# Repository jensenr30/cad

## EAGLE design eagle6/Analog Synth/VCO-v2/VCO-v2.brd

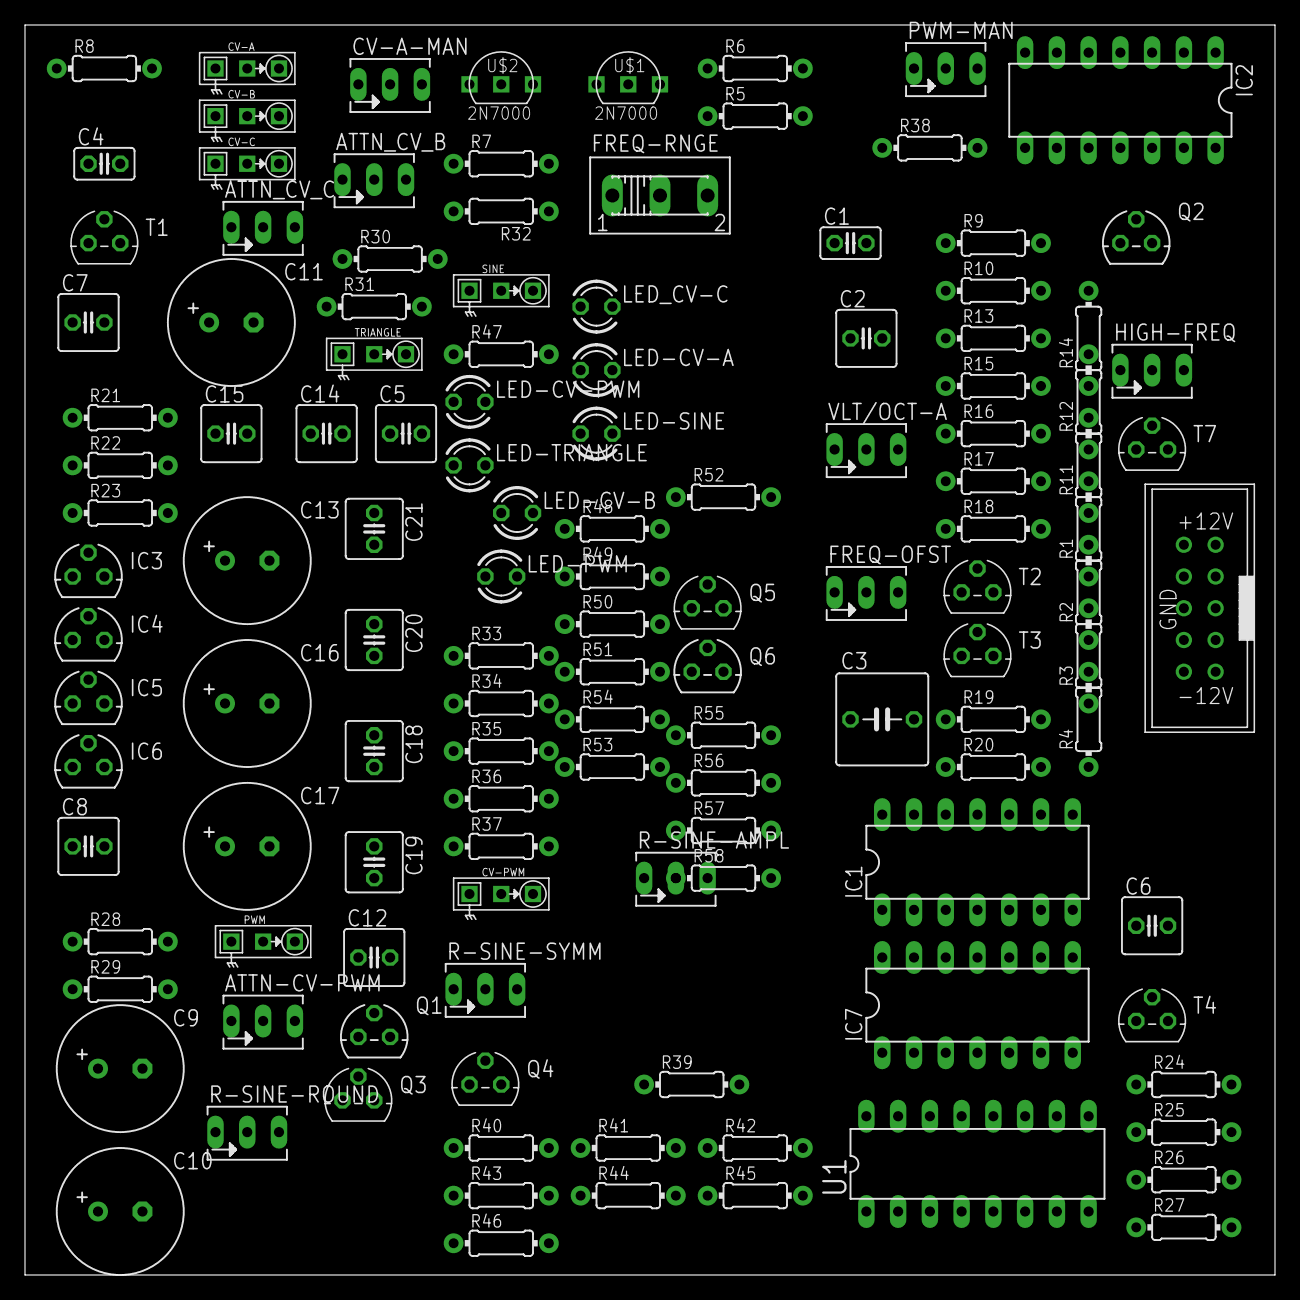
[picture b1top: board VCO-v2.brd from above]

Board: 2 copper layers, 100.0 x 100.0 mm, 127 parts (0 on the bottom side), 79 nets, no tracks yet.

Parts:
ATTN-CV-PWM: 100k log; B64Y
ATTN_CV_B: 100k log; B64Y
ATTN_CV_C: 100k log; B64Y
C1: 10n; C025-025X050
C2: 1u; C025-050X050
C3: 100u; C050-075X075
C4: 100p; C025-025X050
C5: 100p; C025-050X050
C6, C7: 300p; C025-050X050
C8, C12, C14, C15, C18, C19, C20, C21: 0.1u; C025-050X050
C9, C10: 100u; E3,5-10
C11, C13, C16, C17: 10u; E3,5-10
CV-A: I/O; MONO_JACK
CV-A-MAN: 100k lin; B64Y
CV-B: I/O; MONO_JACK
CV-C: I/O; MONO_JACK
CV-PWM: I/O; MONO_JACK
FREQ-OFST: 10k trim; B64Y
FREQ-RNGE: 255SB
HIGH-FREQ: 100k trim; B64Y
IC1, IC2, IC7: TL084P; DIL14
IC3: 78L09; 78LXX
IC4: 78L05; 78LXX
IC5: 79L09\; 79LXX
IC6: 79L05; 79LXX
LED-CV-A: LED3MM
LED-CV-B: LED3MM
LED-CV-PWM: LED3MM
LED-PWM: LED3MM
LED-SINE: LED3MM
LED-TRIANGLE: LED3MM
LED_CV-C: LED3MM
PWM: I/O; MONO_JACK
PWM-MAN: 100k lin; B64Y
Q1, Q2: J310; TO92R
Q3, Q4, Q5: 2N3904; TO92
Q6: 2N3906; TO92
R1, R2, R3, R4, R5, R6, R27, R37, R43, R44, R56, R57: 47k; 0204/7
R7: 150k; 0204/7
R8, R12, R32, R47: 1k; 0204/7
R9, R14, R48, R49, R50, R52, R53, R54: 4.7k; 0204/7
R10, R16, R18, R21, R23, R24, R26, R45, R46: 10k; 0204/7
R11: 22k; 0204/7
R13, R15, R17, R19, R35, R36, R39, R40: 2.2k; 0204/7
R20, R22, R25, R30, R31, R33, R34, R38, R42: 100k; 0204/7
R28, R29: 7.5; 0204/7
R41: 470; 0204/7
R51: 8.2k; 0204/7
R55, R58: 33k; 0204/7
R-SINE-AMPL: 100k trim; B64Y
R-SINE-ROUND: 100k trim; B64Y
R-SINE-SYMM: 10k trim; B64Y
SINE: I/O; MONO_JACK
T1, T2, T3, T4, T7: 2N3904; TO92
TRIANGLE: I/O; MONO_JACK
U1: CA3096; DIL16
U$1, U$2: 2N7000
U$3: EURORACK-POWER
VLT/OCT-A: 10k trim; B64Y

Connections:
+5V: C17.+, C19.1, CV-A-MAN.A, IC4.OUT, PWM-MAN.A, R7.2, U1.10, U1.13
+9V: C11.+, C18.1, IC3.OUT, R16.2, R17.1, R19.2, R43.2, R44.2
+12V: C8.1, C9.+, C14.1, IC1.4, IC2.4, IC3.IN, IC4.IN, Q5.1, R28.2, R58.1
-5V: C1.2, C2.2, C3.2, C16.-, C21.1, CV-A-MAN.E, HIGH-FREQ.E, IC1.12, IC6.OUT, PWM-MAN.E, Q1.S, Q2.S, R22.1, R25.1, T1.3, T2.3, T3.3, U1.5, U1.8
-9V: C13.-, C20.1, IC5.OUT, R9.1, R10.1, R14.1, R42.2
-12V: C10.-, C12.1, C15.1, IC1.11, IC2.11, IC5.IN, IC6.IN, Q6.1, R29.1, R55.2, U1.16
CV-A: IC1.1, IC1.2, LED-CV-A.A, R4.1
CV-B: IC1.6, IC1.7, LED-CV-B.A, R5.1
CV-C: IC1.8, IC1.9, LED_CV-C.A, R6.1
CV-PWM: IC2.13, IC7.1, LED-CV-PWM.K, R38.2
CV_SUM_POINT: FREQ-OFST.A, IC1.13, R5.2, R6.2, R11.1, R12.1, R27.2, VLT/OCT-A.E, VLT/OCT-A.S
GND: ATTN-CV-PWM.A, ATTN_CV_B.A, ATTN_CV_C.A, C8.2, C9.-, C10.+, C11.-, C12.2, C13.+, C14.2, C15.2, C16.+, C17.-, C18.2, C19.2, C20.2, C21.2, CV-A.P$1, CV-B.P$1, CV-B.P$3, CV-C.P$1, CV-C.P$3, CV-PWM.P$1, CV-PWM.P$3, IC2.3, IC3.GND, IC4.GND, IC5.GND, IC6.GND, IC7.3, IC7.12, PWM.P$1, R21.2, R24.2, R30.1, R36.1, R39.2, R40.2, R45.1, R56.1, R57.2, SINE.P$1, T4.1, T4.3, T7.1, T7.3, TRIANGLE.P$1, U$3.P$3, U$3.P$4, U$3.P$5, U$3.P$6, U$3.P$7, U$3.P$8
unnamed: CV-A.P$3, CV-A-MAN.S
unnamed: CV-A.P$2, R1.1
unnamed: IC1.3, IC1.5, IC1.10, R1.2, R2.2, R3.2
unnamed: ATTN_CV_C.S, R3.1
unnamed: Q6.2, R55.1, R56.2
unnamed: ATTN_CV_B.S, R2.1
unnamed: LED-CV-PWM.A, R53.1
unnamed: ATTN_CV_B.E, CV-B.P$2
unnamed: ATTN_CV_C.E, CV-C.P$2
unnamed: Q5.3, R53.2
unnamed: U1.6, U1.11, U1.12, U1.14
unnamed: R4.2, VLT/OCT-A.A
unnamed: C4.2, IC2.1, R8.1
unnamed: R8.2, U1.2, U1.4, U1.7
unnamed: R16.1, T1.1, T2.2
unnamed: FREQ-OFST.E, R14.2
unnamed: C2.1, FREQ-RNGE.3
unnamed: U1.9, U$1.S
unnamed: U1.15, U$2.D
unnamed: C4.1, IC2.2, R7.1, U1.3
unnamed: C3.1, FREQ-RNGE.1
unnamed: R9.2, R10.2, R13.1, R18.1, T1.2
unnamed: R13.2, R15.1
unnamed: Q1.D, R21.1, R23.1
unnamed: C7.2, Q1.G, R22.2, T7.2
unnamed: IC2.9, R30.2, R31.2
unnamed: R32.1, TRIANGLE.P$2
unnamed: Q2.D, R24.1, R26.1
unnamed: C5.2, R20.1, T3.2
unnamed: C6.2, Q2.G, R25.2, T4.2
unnamed: HIGH-FREQ.A, R23.2, R26.2
unnamed: HIGH-FREQ.S, R27.1
unnamed: R28.1, U$3.P$1, U$3.P$2
unnamed: R29.2, U$3.P$9, U$3.P$10
unnamed: Q6.3, R48.2, R49.2, R50.2, R51.2, R52.2, R54.2
unnamed: Q3.2, R39.1, R-SINE-ROUND.E
unnamed: PWM.P$2, R35.2, R36.2
unnamed: IC7.5, R37.2
unnamed: ATTN-CV-PWM.E, IC7.6, IC7.7
unnamed: CV-PWM.P$2, R37.1
unnamed: ATTN-CV-PWM.S, R34.1
unnamed: IC7.2, R33.2, R34.2, R38.1
unnamed: Q5.2, R57.1, R58.2
unnamed: PWM-MAN.S, R33.1
unnamed: Q4.2, R40.1
unnamed: Q3.3, R41.1, R-SINE-SYMM.A
unnamed: Q4.3, R41.2, R-SINE-SYMM.E
unnamed: R42.1, R-SINE-SYMM.S
unnamed: IC7.9, Q3.1, R43.1, R46.1
unnamed: IC7.8, R46.2, R-SINE-AMPL.A
unnamed: IC7.10, Q4.1, R44.1, R45.2
unnamed: LED-CV-A.K, R52.1
unnamed: IC7.13, R-SINE-AMPL.S
unnamed: R47.2, SINE.P$2
unnamed: LED-CV-B.K, R48.1
unnamed: LED_CV-C.K, R49.1
unnamed: LED-TRIANGLE.K, R50.1
unnamed: LED-PWM.K, R51.1
unnamed: LED-SINE.K, R54.1
NPN_CV: IC1.14, R11.2, R12.2, U1.1
PWM: IC2.14, LED-PWM.A, R35.1
RAMP_DOWN: C5.1, C6.1, R17.2, R18.2, R20.2, T2.1, U$1.G
RAMP_UP: C7.1, R19.1, T3.1, U$2.G
SINE: IC7.14, LED-SINE.A, R47.1, R-SINE-AMPL.E
TRIANGLE: IC2.8, IC2.12, LED-TRIANGLE.A, R31.1, R32.2, R-SINE-ROUND.A, R-SINE-ROUND.S
TRIANGLE-RAW: C1.1, FREQ-RNGE.2, IC2.5, U$1.D, U$2.S
V-CAP-BUFF: IC2.6, IC2.7, IC2.10, R15.2

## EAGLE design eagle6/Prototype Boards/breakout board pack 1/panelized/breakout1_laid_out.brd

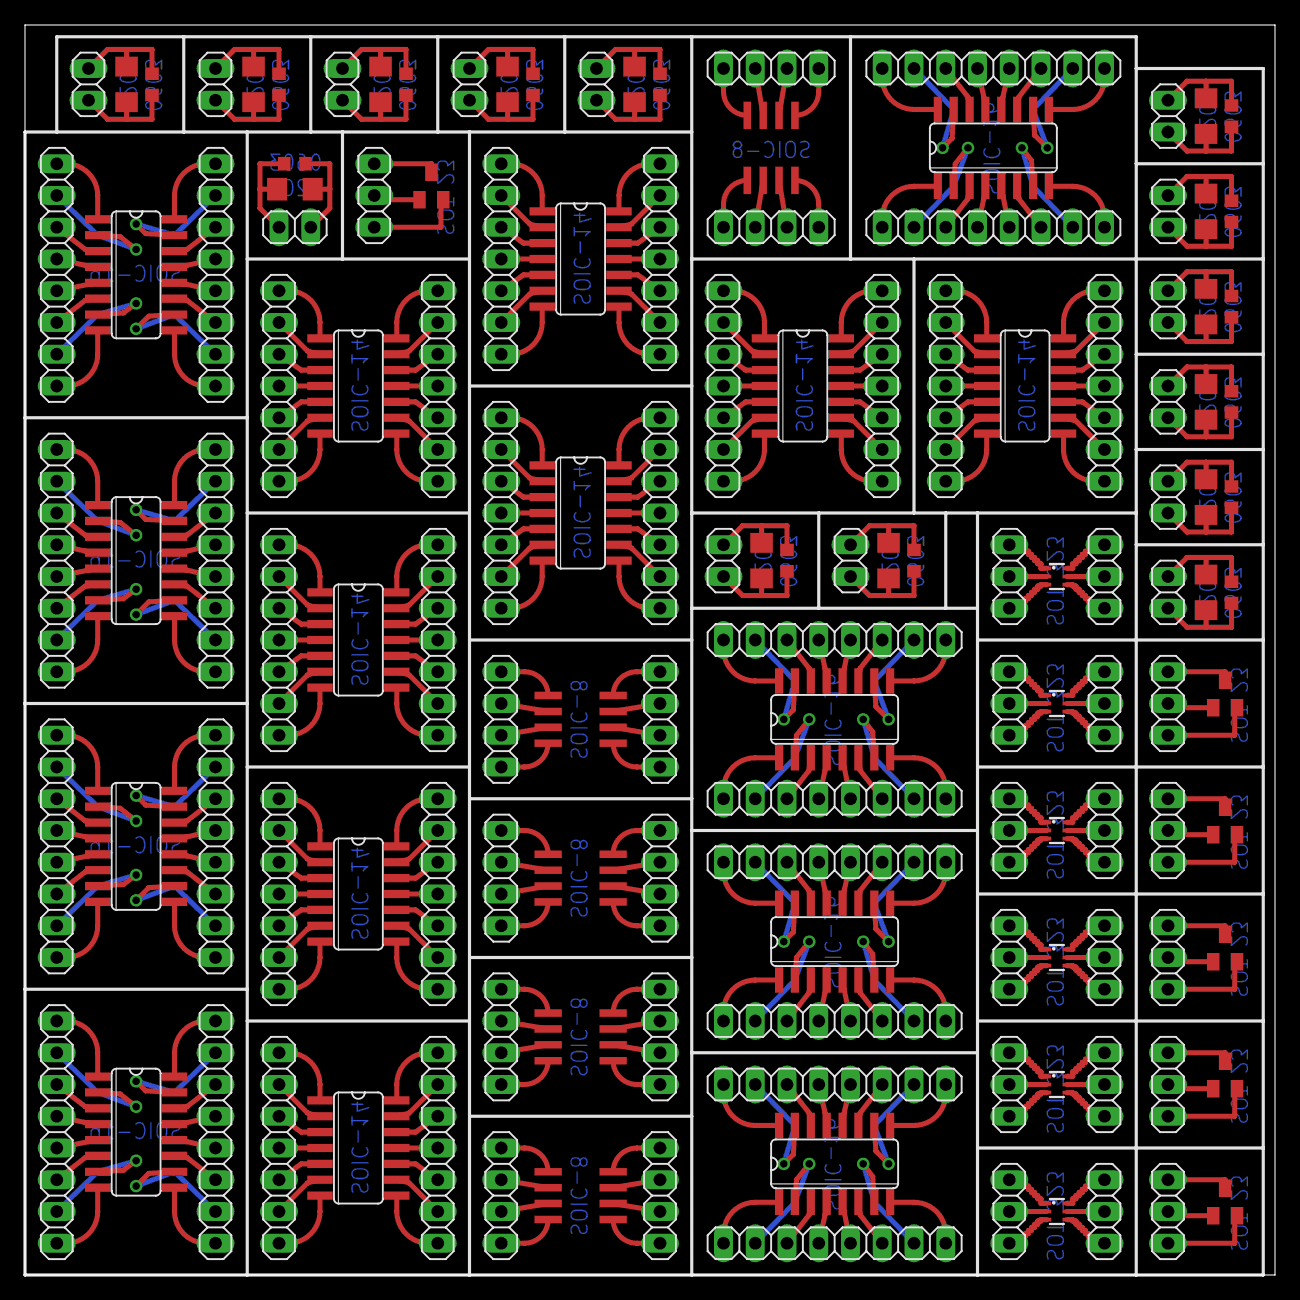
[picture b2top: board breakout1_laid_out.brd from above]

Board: 2 copper layers, 100.0 x 100.0 mm, 135 parts (0 on the bottom side), 362 nets.

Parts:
IC1, IC4, IC5, IC13, IC21, IC22, IC23, IC26: 74LS151D; SO16
IC3, IC10, IC17, IC18, IC27: NE555D; SO08
IC7, IC8, IC14, IC15, IC16, IC19, IC24, IC25: 74LS03D; SO14
JP1, JP2, JP31, JP32, JP49, JP50, JP51, JP52, JP53, JP66, JP67, JP68, JP69, JP70, JP71, JP72, JP73, JP91: 1X03
JP5, JP6, JP11, JP12, JP13, JP14, JP41, JP42, JP74, JP75, JP76, JP77, JP78, JP79, JP86, JP87: 1X08
JP9, JP10, JP35, JP36, JP57, JP58, JP59, JP60, JP88, JP89: 1X04
JP17, JP18, JP19, JP20, JP43, JP44, JP45, JP46, JP47, JP48, JP61, JP62, JP82, JP83, JP84, JP85: 1X07
JP23, JP24, JP25, JP54, JP55, JP56, JP63, JP65, JP80, JP81, JP92, JP93, JP94, JP95: 1X02
Q5, Q6, Q7, Q8, Q9, Q10: BCX70SMD; SOT23
R1, R5, R7, R9, R11, R13, R15, R17, R19, R21, R23, R25, R27, R29: R0603
R3, R6, R8, R10, R12, R14, R16, R18, R20, R22, R24, R26, R28, R30: R1206
U$1, U$3, U$5, U$6, U$7, U$8: DMMT3904W; SOT363

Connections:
unnamed: JP1.3, U$1.1
unnamed: JP1.2, U$1.2
unnamed: JP1.1, U$1.3
unnamed: JP2.1, U$1.4
unnamed: JP2.2, U$1.5
unnamed: JP2.3, U$1.6
unnamed: IC4.1, JP12.1
unnamed: IC1.1, JP6.1
unnamed: IC1.2, JP6.2
unnamed: IC1.3, JP6.3
unnamed: IC1.4, JP6.4
unnamed: IC1.7, JP6.7
unnamed: IC1.5, JP6.5
unnamed: IC1.6, JP6.6
unnamed: IC1.8, JP6.8
unnamed: IC1.9, JP5.1
unnamed: IC1.10, JP5.2
unnamed: IC1.11, JP5.3
unnamed: IC1.12, JP5.4
unnamed: IC1.13, JP5.5
unnamed: IC1.14, JP5.6
unnamed: IC1.15, JP5.7
unnamed: IC1.16, JP5.8
unnamed: IC3.1, JP9.1
unnamed: IC3.2, JP9.2
unnamed: IC3.4, JP9.4
unnamed: IC3.3, JP9.3
unnamed: IC3.5, JP10.1
unnamed: IC3.6, JP10.2
unnamed: IC3.7, JP10.3
unnamed: IC3.8, JP10.4
unnamed: IC4.2, JP12.2
unnamed: IC4.3, JP12.3
unnamed: IC4.4, JP12.4
unnamed: IC4.7, JP12.7
unnamed: IC4.5, JP12.5
unnamed: IC4.6, JP12.6
unnamed: IC4.8, JP12.8
unnamed: IC4.9, JP11.1
unnamed: IC4.10, JP11.2
unnamed: IC4.11, JP11.3
unnamed: IC4.12, JP11.4
unnamed: IC4.13, JP11.5
unnamed: IC4.14, JP11.6
unnamed: IC4.16, JP11.8
unnamed: IC4.15, JP11.7
unnamed: IC5.1, JP14.1
unnamed: IC5.2, JP14.2
unnamed: IC5.3, JP14.3
unnamed: IC5.4, JP14.4
unnamed: IC5.7, JP14.7
unnamed: IC5.5, JP14.5
unnamed: IC5.6, JP14.6
unnamed: IC5.8, JP14.8
unnamed: IC5.9, JP13.1
unnamed: IC5.10, JP13.2
unnamed: IC5.11, JP13.3
unnamed: IC5.12, JP13.4
unnamed: IC5.13, JP13.5
unnamed: IC5.14, JP13.6
unnamed: IC5.16, JP13.8
unnamed: IC5.15, JP13.7
unnamed: IC7.1, JP17.1
unnamed: IC7.2, JP17.2
unnamed: IC7.4, JP17.4
unnamed: IC7.5, JP17.5
unnamed: IC7.6, JP17.6
unnamed: IC7.3, JP17.3
unnamed: IC7.8, JP18.1
unnamed: IC7.9, JP18.2
unnamed: IC7.10, JP18.3
unnamed: IC7.11, JP18.4
unnamed: IC7.12, JP18.5
unnamed: IC7.13, JP18.6
unnamed: IC7.14, JP18.7
unnamed: IC7.7, JP17.7
unnamed: IC8.1, JP19.1
unnamed: IC8.2, JP19.2
unnamed: IC8.4, JP19.4
unnamed: IC8.5, JP19.5
unnamed: IC8.6, JP19.6
unnamed: IC8.3, JP19.3
unnamed: IC8.8, JP20.1
unnamed: IC8.9, JP20.2
unnamed: IC8.10, JP20.3
unnamed: IC8.11, JP20.4
unnamed: IC8.12, JP20.5
unnamed: IC8.13, JP20.6
unnamed: IC8.14, JP20.7
unnamed: IC8.7, JP19.7
unnamed: JP23.1, R1.2, R3.2
unnamed: JP23.2, R1.1, R3.1
unnamed: JP24.1, R5.2, R6.2
unnamed: JP24.2, R5.1, R6.1
unnamed: JP25.1, R7.2, R8.2
unnamed: JP25.2, R7.1, R8.1
unnamed: JP31.1, U$3.3
unnamed: JP31.2, U$3.2
unnamed: JP31.3, U$3.1
unnamed: JP32.1, U$3.4
unnamed: JP32.2, U$3.5
unnamed: JP32.3, U$3.6
unnamed: IC10.1, JP35.1
unnamed: IC10.2, JP35.2
unnamed: IC10.4, JP35.4
unnamed: IC10.3, JP35.3
unnamed: IC10.5, JP36.1
unnamed: IC10.6, JP36.2
unnamed: IC10.7, JP36.3
unnamed: IC10.8, JP36.4
unnamed: IC13.1, JP42.1
unnamed: IC13.2, JP42.2
unnamed: IC13.3, JP42.3
unnamed: IC13.4, JP42.4
unnamed: IC13.7, JP42.7
unnamed: IC13.5, JP42.5
unnamed: IC13.6, JP42.6
unnamed: IC13.8, JP42.8
unnamed: IC13.9, JP41.1
unnamed: IC13.10, JP41.2
unnamed: IC13.11, JP41.3
unnamed: IC13.12, JP41.4
unnamed: IC13.13, JP41.5
unnamed: IC13.14, JP41.6
unnamed: IC13.16, JP41.8
unnamed: IC13.15, JP41.7
unnamed: IC14.1, JP43.1
unnamed: IC14.2, JP43.2
unnamed: IC14.4, JP43.4
unnamed: IC14.5, JP43.5
unnamed: IC14.6, JP43.6
unnamed: IC14.3, JP43.3
unnamed: IC14.8, JP44.1
unnamed: IC14.9, JP44.2
unnamed: IC14.10, JP44.3
unnamed: IC14.11, JP44.4
unnamed: IC14.12, JP44.5
unnamed: IC14.13, JP44.6
unnamed: IC14.14, JP44.7
unnamed: IC14.7, JP43.7
unnamed: IC15.1, JP45.1
unnamed: IC15.2, JP45.2
unnamed: IC15.4, JP45.4
unnamed: IC15.5, JP45.5
unnamed: IC15.6, JP45.6
unnamed: IC15.3, JP45.3
unnamed: IC15.8, JP46.1
unnamed: IC15.9, JP46.2
unnamed: IC15.10, JP46.3
unnamed: IC15.11, JP46.4
unnamed: IC15.12, JP46.5
unnamed: IC15.13, JP46.6
unnamed: IC15.14, JP46.7
unnamed: IC15.7, JP45.7
unnamed: IC16.1, JP47.1
unnamed: IC16.2, JP47.2
unnamed: IC16.4, JP47.4
unnamed: IC16.5, JP47.5
unnamed: IC16.6, JP47.6
unnamed: IC16.3, JP47.3
unnamed: IC16.8, JP48.1
unnamed: IC16.9, JP48.2
unnamed: JP49.2, Q5.1
unnamed: JP49.3, Q5.2
unnamed: JP49.1, Q5.3
unnamed: JP50.2, Q6.1
unnamed: JP50.3, Q6.2
unnamed: JP50.1, Q6.3
unnamed: JP51.2, Q7.1
unnamed: JP51.3, Q7.2
unnamed: JP51.1, Q7.3
unnamed: JP52.2, Q8.1
unnamed: JP52.3, Q8.2
unnamed: JP52.1, Q8.3
unnamed: JP53.2, Q9.1
unnamed: JP53.3, Q9.2
unnamed: JP53.1, Q9.3
unnamed: JP54.1, R13.2, R14.2
unnamed: JP54.2, R13.1, R14.1
unnamed: JP65.1, R15.2, R16.2
unnamed: JP55.1, R9.2, R10.2
unnamed: JP55.2, R9.1, R10.1
unnamed: JP56.1, R11.2, R12.2
unnamed: JP56.2, R11.1, R12.1
unnamed: JP65.2, R15.1, R16.1
unnamed: JP66.1, U$5.3
unnamed: IC17.1, JP57.1
unnamed: IC17.2, JP57.2
unnamed: IC17.4, JP57.4
unnamed: IC17.3, JP57.3
unnamed: IC17.5, JP58.1
unnamed: IC17.6, JP58.2
unnamed: IC17.7, JP58.3
unnamed: IC17.8, JP58.4
unnamed: IC18.1, JP59.1
unnamed: IC18.2, JP59.2
unnamed: IC18.4, JP59.4
unnamed: IC18.3, JP59.3
unnamed: IC18.5, JP60.1
unnamed: IC18.6, JP60.2
unnamed: IC18.7, JP60.3
unnamed: IC18.8, JP60.4
unnamed: IC19.1, JP61.1
unnamed: IC19.2, JP61.2
unnamed: IC19.4, JP61.4
unnamed: IC19.5, JP61.5
unnamed: IC19.6, JP61.6
unnamed: IC19.3, JP61.3
unnamed: IC19.8, JP62.1
unnamed: IC19.9, JP62.2
unnamed: IC19.10, JP62.3
unnamed: IC19.11, JP62.4
unnamed: IC19.12, JP62.5
unnamed: IC19.13, JP62.6
unnamed: IC19.14, JP62.7
unnamed: IC19.7, JP61.7
unnamed: IC16.10, JP48.3
unnamed: IC16.11, JP48.4
unnamed: IC16.12, JP48.5
unnamed: IC16.13, JP48.6
unnamed: IC16.14, JP48.7
unnamed: IC16.7, JP47.7
unnamed: JP63.1, R21.2, R22.2
unnamed: JP63.2, R21.1, R22.1
unnamed: JP91.2, Q10.1
unnamed: JP66.2, U$5.2
unnamed: JP66.3, U$5.1
unnamed: JP67.1, U$5.4
unnamed: JP67.2, U$5.5
unnamed: JP67.3, U$5.6
unnamed: JP68.1, U$6.3
unnamed: JP68.2, U$6.2
unnamed: JP68.3, U$6.1
unnamed: JP69.1, U$6.4
unnamed: JP69.2, U$6.5
unnamed: JP69.3, U$6.6
unnamed: JP70.1, U$7.3
unnamed: JP70.2, U$7.2
unnamed: JP70.3, U$7.1
unnamed: JP71.1, U$7.4
unnamed: JP71.2, U$7.5
unnamed: JP71.3, U$7.6
unnamed: JP72.1, U$8.3
unnamed: JP72.2, U$8.2
unnamed: JP72.3, U$8.1
unnamed: JP73.1, U$8.4
unnamed: JP73.2, U$8.5
unnamed: JP73.3, U$8.6
unnamed: IC21.1, JP75.1
unnamed: IC21.2, JP75.2
unnamed: IC21.3, JP75.3
unnamed: IC21.4, JP75.4
unnamed: IC21.7, JP75.7
unnamed: IC21.5, JP75.5
unnamed: IC21.6, JP75.6
unnamed: IC21.8, JP75.8
unnamed: IC21.9, JP74.1
unnamed: IC21.10, JP74.2
unnamed: IC21.11, JP74.3
unnamed: IC21.12, JP74.4
unnamed: IC21.13, JP74.5
unnamed: IC21.14, JP74.6
unnamed: IC21.16, JP74.8
unnamed: IC21.15, JP74.7
unnamed: IC22.1, JP77.1
unnamed: IC22.2, JP77.2
unnamed: IC22.3, JP77.3
unnamed: IC22.4, JP77.4
unnamed: IC22.7, JP77.7
unnamed: IC22.5, JP77.5
unnamed: IC22.6, JP77.6
unnamed: IC22.8, JP77.8
unnamed: IC22.9, JP76.1
unnamed: IC22.10, JP76.2
unnamed: IC22.11, JP76.3
unnamed: IC22.12, JP76.4
unnamed: IC22.13, JP76.5
unnamed: IC22.14, JP76.6
unnamed: IC22.16, JP76.8
unnamed: IC22.15, JP76.7
unnamed: IC23.1, JP79.1
unnamed: IC23.2, JP79.2
unnamed: IC23.3, JP79.3
unnamed: IC23.4, JP79.4
unnamed: IC23.7, JP79.7
unnamed: IC23.5, JP79.5
unnamed: IC23.6, JP79.6
unnamed: IC23.8, JP79.8
unnamed: IC23.9, JP78.1
unnamed: IC23.10, JP78.2
unnamed: IC23.11, JP78.3
unnamed: IC23.12, JP78.4
unnamed: IC23.13, JP78.5
unnamed: IC23.14, JP78.6
unnamed: IC23.16, JP78.8
unnamed: IC23.15, JP78.7
unnamed: JP80.1, R17.2, R18.2
unnamed: JP80.2, R17.1, R18.1
unnamed: JP81.1, R19.2, R20.2
unnamed: JP81.2, R19.1, R20.1
unnamed: IC24.1, JP82.1
unnamed: IC24.2, JP82.2
unnamed: IC24.4, JP82.4
unnamed: IC24.5, JP82.5
unnamed: IC24.6, JP82.6
unnamed: IC24.3, JP82.3
unnamed: IC24.8, JP83.1
unnamed: IC24.9, JP83.2
unnamed: IC24.10, JP83.3
unnamed: IC24.11, JP83.4
unnamed: IC24.12, JP83.5
unnamed: IC24.13, JP83.6
unnamed: IC24.14, JP83.7
unnamed: IC24.7, JP82.7
unnamed: IC25.1, JP84.1
unnamed: IC25.2, JP84.2
unnamed: IC25.4, JP84.4
unnamed: IC25.5, JP84.5
unnamed: IC25.6, JP84.6
unnamed: IC25.3, JP84.3
unnamed: IC25.8, JP85.1
unnamed: IC25.9, JP85.2
unnamed: IC25.10, JP85.3
unnamed: IC25.11, JP85.4
unnamed: IC25.12, JP85.5
unnamed: IC25.13, JP85.6
unnamed: IC25.14, JP85.7
unnamed: IC25.7, JP84.7
unnamed: IC26.1, JP87.1
unnamed: IC26.2, JP87.2
unnamed: IC26.3, JP87.3
unnamed: IC26.4, JP87.4
unnamed: IC26.7, JP87.7
unnamed: IC26.5, JP87.5
unnamed: IC26.6, JP87.6
unnamed: IC26.8, JP87.8
unnamed: IC26.9, JP86.1
unnamed: IC26.10, JP86.2
unnamed: IC26.11, JP86.3
unnamed: IC26.12, JP86.4
unnamed: IC26.13, JP86.5
unnamed: IC26.14, JP86.6
unnamed: IC26.16, JP86.8
unnamed: IC26.15, JP86.7
unnamed: IC27.1, JP88.1
unnamed: IC27.2, JP88.2
unnamed: IC27.4, JP88.4
unnamed: IC27.3, JP88.3
unnamed: IC27.5, JP89.1
unnamed: IC27.6, JP89.2
unnamed: IC27.7, JP89.3
unnamed: IC27.8, JP89.4
unnamed: JP91.3, Q10.2
unnamed: JP91.1, Q10.3
unnamed: JP92.1, R23.2, R24.2
unnamed: JP92.2, R23.1, R24.1
unnamed: JP93.1, R25.2, R26.2
unnamed: JP93.2, R25.1, R26.1
unnamed: JP94.1, R27.2, R28.2
unnamed: JP94.2, R27.1, R28.1
unnamed: JP95.1, R29.2, R30.2
unnamed: JP95.2, R29.1, R30.1
